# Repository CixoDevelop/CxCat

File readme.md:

# CxCat
It is robotic toy for Cats.

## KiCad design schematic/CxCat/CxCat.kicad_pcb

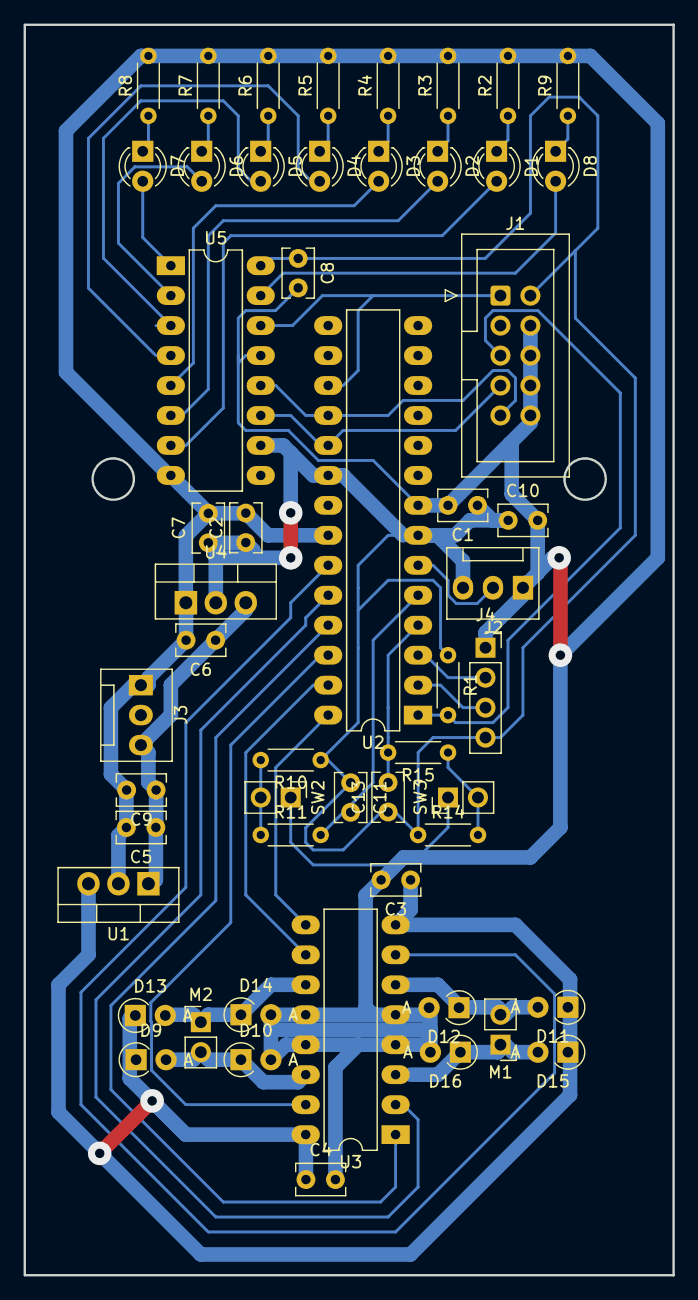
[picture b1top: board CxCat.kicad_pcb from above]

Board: 2 copper layers, 55.0 x 106.0 mm, 54 parts (0 on the bottom side), 41 nets.

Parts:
C1, C2, C6: 10uF; C_Rect_L4.0mm_W2.5mm_P2.50mm
C3, C4, C5, C7, C10: 100uF; C_Rect_L4.0mm_W2.5mm_P2.50mm
C8, C11, C13: 50pF; C_Rect_L4.0mm_W2.5mm_P2.50mm
C9: 2200uF; C_Rect_L4.0mm_W2.5mm_P2.50mm
D1, D2, D3, D4, D5, D6, D7, D8: LED; LED_D3.0mm
D9, D10, D11, D12, D13, D14, D15, D16: 1N4007; D_A-405_P2.54mm_Vertical_AnodeUp
J1: AVR-ISP-10; IDC-Header_2x05_P2.54mm_Vertical
J2, J3: Conn_01x03; FanPinHeader_1x03_P2.54mm_Vertical
J4: Conn_01x04_Pin; PinSocket_1x04_P2.54mm_Vertical
M1, M2: Motor_DC; PinHeader_1x02_P2.54mm_Vertical
R1, R10, R11, R14, R15: 10K; R_Axial_DIN0204_L3.6mm_D1.6mm_P5.08mm_Horizontal
R2, R3, R4, R5, R6, R7, R8, R9: 560R; R_Axial_DIN0204_L3.6mm_D1.6mm_P5.08mm_Horizontal
SW2, SW3: SW_Omron_B3FS; PinHeader_1x02_P2.54mm_Vertical
U1: L7805; TO-220-3_Vertical
U2: ATmega8A-P; DIP-28_W7.62mm_LongPads
U3: L293D; DIP-16_W7.62mm_LongPads
U4: LM1117-5.0; TO-220-3_Vertical
U5: 74HC595; DIP-16_W7.62mm_LongPads

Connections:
+5V: C1.1, C2.1, C7.1, C8.1, C10.1, C11.1, C13.1, J1.2 (VCC), J2.3, J4.4, R1.1, R10.1, R14.1, U2.7 (VCC), U2.20 (AVCC), U4.2 (VO), U5.10 (~SRCLR), U5.16 (VCC)
/Engines/1: U2.24 (PC1), U3.2 (1A)
/Engines/1-2 ENABLE: U2.25 (PC2), U3.1 (EN1,2)
/Engines/2: U2.23 (PC0), U3.7 (2A)
/Engines/3: U2.27 (PC4), U3.10 (3A)
/Engines/3-4 ENABLE: U2.28 (PC5), U3.9 (EN3,4)
/Engines/4: U2.26 (PC3), U3.15 (4A)
/Eyes/CLOCK: J1.7 (SCK), U2.19 (PB5), U5.11 (SRCLK)
/Eyes/DATA: J1.1 (MOSI), U2.17 (PB3), U5.14 (SER)
/Eyes/LATCH: J1.9 (MISO), U2.18 (PB4), U5.12 (RCLK)
/Input left/STATE: C13.2, R15.2, U2.4 (PD2)
/Input right/STATE: C11.2, R11.2, U2.5 (PD3)
GND: C1.2, C2.2, C3.2, C4.2, C5.2, C6.2, C7.2, C8.2, C9.2, C10.2, D10.2 (A), D12.2 (A), D14.2 (A), D16.2 (A), J1.4 (GND), J1.6 (GND), J1.8 (GND), J1.10 (GND), J2.1, J3.1, J4.1, R2.2, R3.2, R4.2, R5.2, R6.2, R7.2, R8.2, R9.2, SW2.1, SW3.1, U1.2 (GND), U2.8 (GND), U2.22 (AGND), U3.4 (GND), U3.5 (GND), U3.12 (GND), U3.13 (GND), U4.1 (GND), U5.8 (GND), U5.13 (~OE)
unnamed: D1.2 (A), U5.7 (QH)
unnamed: D1.1 (K), R2.1
unnamed: D2.2 (A), U5.6 (QG)
unnamed: D2.1 (K), R3.1
unnamed: D3.2 (A), U5.5 (QF)
unnamed: D3.1 (K), R4.1
unnamed: D4.2 (A), U5.4 (QE)
unnamed: D4.1 (K), R5.1
unnamed: D5.2 (A), U5.3 (QD)
unnamed: D5.1 (K), R6.1
unnamed: D6.2 (A), U5.2 (QC)
unnamed: D6.1 (K), R7.1
unnamed: D7.2 (A), U5.1 (QB)
unnamed: D7.1 (K), R8.1
unnamed: D8.2 (A), U5.15 (QA)
unnamed: D8.1 (K), R9.1
unnamed: D9.2 (A), D10.1 (K), M2.2 (-), U3.14 (4Y)
unnamed: D11.2 (A), D12.1 (K), M1.2 (-), U3.6 (2Y)
unnamed: C3.1, C4.1, D9.1 (K), D11.1 (K), D13.1 (K), D15.1 (K), U1.3 (OUT), U3.8 (VCC2), U3.16 (VCC1)
unnamed: D13.2 (A), D14.1 (K), M2.1 (+), U3.11 (3Y)
unnamed: D15.2 (A), D16.1 (K), M1.1 (+), U3.3 (1Y)
unnamed: J1.5 (~RST), R1.2, U2.1 (PC6/~RESET)
unnamed: J2.2, U2.6 (PD4)
unnamed: J4.2, U2.3 (PD1)
unnamed: J4.3, U2.2 (PD0)
unnamed: R10.2, R11.1, SW2.2
unnamed: R14.2, R15.1, SW3.2
VCC: C5.1, C6.1, C9.1, J3.3, U1.1 (IN), U4.3 (VI)

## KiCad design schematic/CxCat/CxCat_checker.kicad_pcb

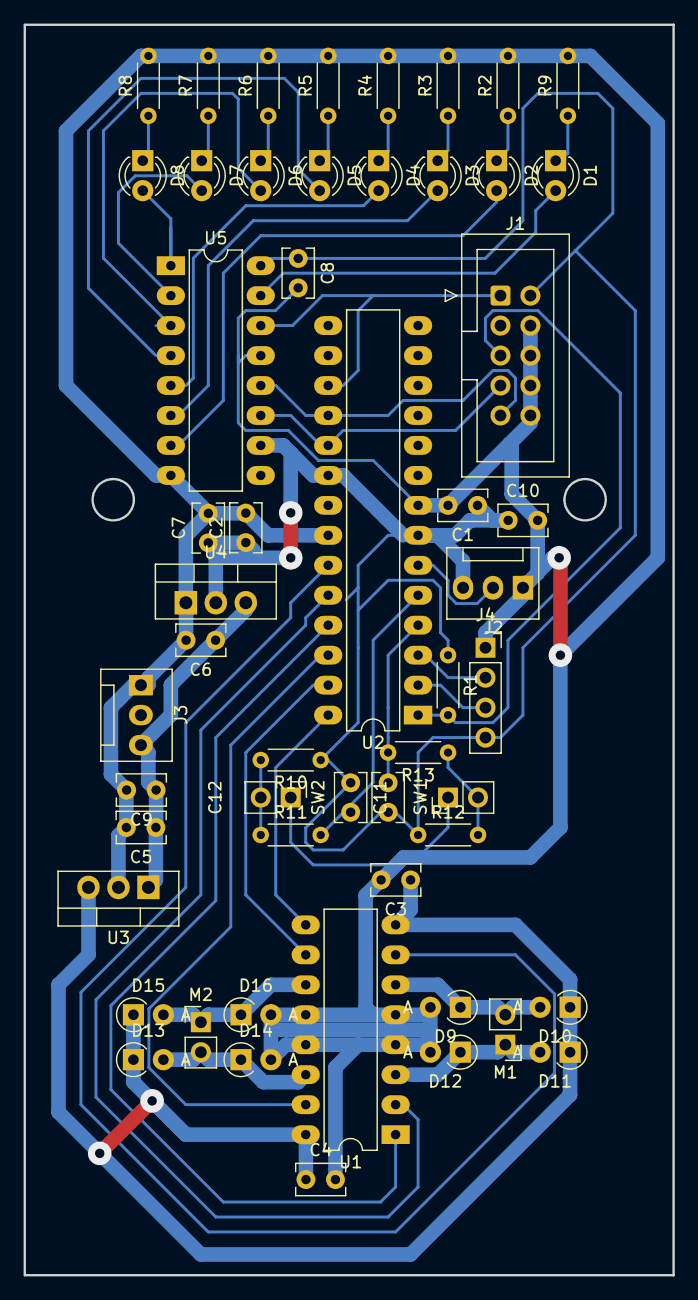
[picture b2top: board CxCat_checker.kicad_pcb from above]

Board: 2 copper layers, 55.0 x 106.0 mm, 54 parts (0 on the bottom side), 41 nets.

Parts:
C1, C2, C3, C4, C5, C6, C7, C8, C9, C10, C11, C12: C; C_Rect_L4.0mm_W2.5mm_P2.50mm
D1, D2, D3, D4, D5, D6, D7, D8: LED; LED_D3.0mm
D9, D10, D11, D12, D13, D14, D15, D16: D; D_A-405_P2.54mm_Vertical_AnodeUp
J1: AVR-ISP-10; IDC-Header_2x05_P2.54mm_Vertical
J2, J3: Conn_01x03; FanPinHeader_1x03_P2.54mm_Vertical
J4: Conn_01x04_Pin; PinSocket_1x04_P2.54mm_Vertical
M1, M2: Motor_DC; PinHeader_1x02_P2.54mm_Vertical
R1, R2, R3, R4, R5, R6, R7, R8, R9, R10, R11, R12, R13: R; R_Axial_DIN0204_L3.6mm_D1.6mm_P5.08mm_Horizontal
SW1, SW2: SW_Omron_B3FS; PinHeader_1x02_P2.54mm_Vertical
U1: L293D; DIP-16_W7.62mm_LongPads
U2: ATmega8A-P; DIP-28_W7.62mm_LongPads
U3: L7805; TO-220-3_Vertical
U4: LM1117-5.0; TO-220-3_Vertical
U5: 74HC595; DIP-16_W7.62mm_LongPads

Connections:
+5V: C1.1, C2.1, C7.1, C8.1, C10.1, C11.1, C12.1, J1.2 (VCC), J2.3, J4.4, R1.1, R10.1, R12.1, U2.7 (VCC), U2.20 (AVCC), U4.2 (VO), U5.10 (~SRCLR), U5.16 (VCC)
GND: C1.2, C2.2, C3.2, C4.2, C5.2, C6.2, C7.2, C8.2, C9.2, C10.2, D9.2 (A), D12.2 (A), D14.2 (A), D16.2 (A), J1.4 (GND), J1.6 (GND), J1.8 (GND), J1.10 (GND), J2.1, J3.1, J4.1, R2.2, R3.2, R4.2, R5.2, R6.2, R7.2, R8.2, R9.2, SW1.1, SW2.1, U1.4 (GND), U1.5 (GND), U1.12 (GND), U1.13 (GND), U2.8 (GND), U2.22 (AGND), U3.2 (GND), U4.1 (GND), U5.8 (GND), U5.13 (~OE)
unnamed: D1.2 (A), U5.15 (QA)
unnamed: D1.1 (K), R9.1
unnamed: D2.2 (A), U5.7 (QH)
unnamed: D2.1 (K), R2.1
unnamed: D3.2 (A), U5.6 (QG)
unnamed: D3.1 (K), R3.1
unnamed: D4.2 (A), U5.5 (QF)
unnamed: D4.1 (K), R4.1
unnamed: D5.2 (A), U5.4 (QE)
unnamed: D5.1 (K), R5.1
unnamed: D6.2 (A), U5.3 (QD)
unnamed: D6.1 (K), R6.1
unnamed: D7.2 (A), U5.2 (QC)
unnamed: D7.1 (K), R7.1
unnamed: D8.2 (A), U5.1 (QB)
unnamed: D8.1 (K), R8.1
unnamed: D9.1 (K), D10.2 (A), M1.2 (-), U1.6 (2Y)
unnamed: C3.1, C4.1, D10.1 (K), D11.1 (K), D13.1 (K), D15.1 (K), U1.8 (VCC2), U1.16 (VCC1), U3.3 (OUT)
unnamed: D11.2 (A), D12.1 (K), M1.1 (+), U1.3 (1Y)
unnamed: D13.2 (A), D14.1 (K), M2.2 (-), U1.14 (4Y)
unnamed: D15.2 (A), D16.1 (K), M2.1 (+), U1.11 (3Y)
unnamed: J1.9 (MISO), U2.18 (PB4), U5.12 (RCLK)
unnamed: J1.1 (MOSI), U2.17 (PB3), U5.14 (SER)
unnamed: J1.7 (SCK), U2.19 (PB5), U5.11 (SRCLK)
unnamed: J1.5 (~RST), R1.2, U2.1 (PC6/~RESET)
unnamed: J2.2, U2.6 (PD4)
unnamed: J4.2, U2.3 (PD1)
unnamed: J4.3, U2.2 (PD0)
unnamed: R10.2, R11.1, SW2.2
unnamed: R12.2, R13.1, SW1.2
unnamed: U1.2 (1A), U2.24 (PC1)
unnamed: U1.7 (2A), U2.23 (PC0)
unnamed: U1.10 (3A), U2.27 (PC4)
unnamed: U1.15 (4A), U2.26 (PC3)
unnamed: U1.1 (EN1,2), U2.25 (PC2)
unnamed: U1.9 (EN3,4), U2.28 (PC5)
unnamed: C12.2, R13.2, U2.4 (PD2)
unnamed: C11.2, R11.2, U2.5 (PD3)
VCC: C5.1, C6.1, C9.1, J3.3, U3.1 (IN), U4.3 (VI)

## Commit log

2023-03-15 Init commit
2023-03-15 Add readme
2023-03-22 Time commit
2023-03-23 New changes, add working head
2023-04-04 Add new feautured, and clean up code
2023-04-04 Update libs, and change buadrate
2023-04-12 Continue work on project
2023-04-12 Add AI driver
2023-04-13 Fix added feautures, code for atmega is ready to clean up and deploy. Start working on ESP8266 firmware
